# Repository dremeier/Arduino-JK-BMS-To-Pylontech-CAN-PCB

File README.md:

<div align = center>

# [Arduino JK-BMS to Pylontech-CAN PCB](https://github.com/dremeier/Arduino-JK-BMS-To-Pylontech-CAN-PCB) 

PCB and Case for the Arduino JK-BMS To Pylontech-CAN converter for Deye Inverter
<br/>

<br/>
<div align = left>
  
## Arduino Firmware by Armin: https://github.com/ArminJo/JK-BMSToPylontechCAN 

#### If you find this program useful, please give it a star.

&#x1F30E; [Google Translate](https://translate.google.com/translate?sl=en&u=https://github.com/dremeier/Arduino-JK-BMS-To-Pylontech-CAN-PCB)

## Features 
- Buck converter for up to 65 Volt to 5V.
- RS232-stream from the BMS translate from 3,3V to 5V and are galvanic seperated.
- MCU ATmega644P with [MightyCore](https://github.com/MCUdude/MightyCore) Bootloader.
- Connectors are JST PH S4B-PH-K 1x04 P2.00mm Horizontal.
- RJ45 connector Amphenol 54602-x08 Horizontal.
- Designed with KiCad 8.

[Files to print your own case](JK-BMS-CAN_Case/)

## Pictures

### PCB Layout

### Aufbau im Gehäuse

### Fertig installiert mit einem BMS, die Verarbeitung für das 2. BMS ist in Arbeit

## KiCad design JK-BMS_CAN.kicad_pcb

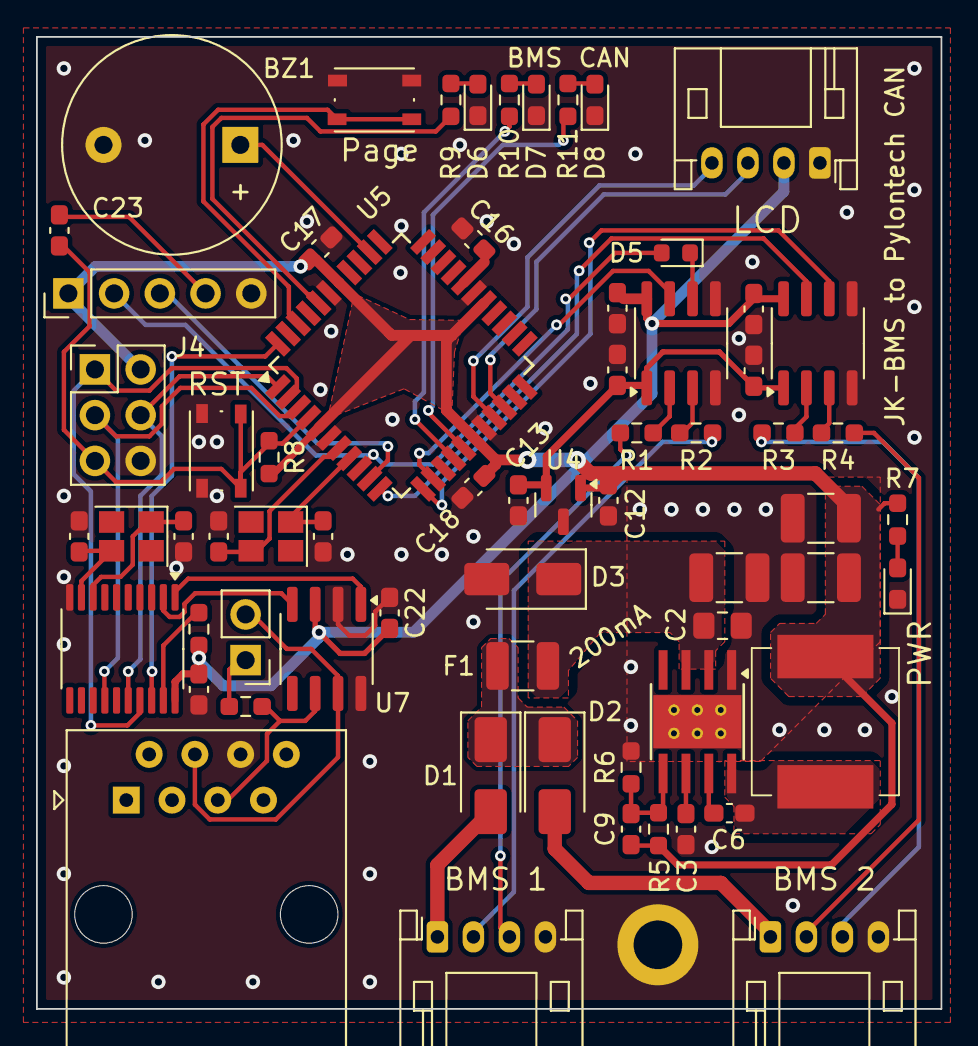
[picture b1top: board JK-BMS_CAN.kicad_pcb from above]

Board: 2 copper layers, 50.2 x 54.0 mm, 66 parts (0 on the bottom side), 53 nets.

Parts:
BZ1: Buzzer; Buzzer_12x9.5RM7.6
C1: 4.7µF/100V; C_1210_3225Metric_Pad1.33x2.70mm_HandSolder
C2: 220nF; C_0805_2012Metric_Pad1.18x1.45mm_HandSolder
C3: 4,7µF/10V; C_0603_1608Metric_Pad1.08x0.95mm_HandSolder
C4, C5, C6, C7, C8, C16, C17, C18, C21, C22, C23: 100nF; C_0603_1608Metric_Pad1.08x0.95mm_HandSolder
C9, C14, C15, C19, C20: 18pF; C_0603_1608Metric_Pad1.08x0.95mm_HandSolder
C10, C11: 47µF/16V; C_1210_3225Metric_Pad1.33x2.70mm_HandSolder
C12, C13: 2,2µF/6,3V; C_0603_1608Metric_Pad1.08x0.95mm_HandSolder
D1, D2: ES2BA; D_SMA
D3: SM6T68A; D_SMA
D4, D7: green 5mA; LED_0603_1608Metric_Pad1.05x0.95mm_HandSolder
D5: CDBU00340; D_0603_1608Metric
D6: red 5mA; LED_0603_1608Metric_Pad1.05x0.95mm_HandSolder
D8: orange 5mA; LED_0603_1608Metric_Pad1.05x0.95mm_HandSolder
F1: 1210L020/72WR; Fuse_1210_3225Metric
H1: MountingHole_Pad; MountingHole_2.7mm_M2.5_ISO7380_Pad
J1: BMS1; JST_PH_S4B-PH-K_1x04_P2.00mm_Horizontal
J2: BMS2; JST_PH_S4B-PH-K_1x04_P2.00mm_Horizontal
J3: Flash; PinHeader_1x05_P2.54mm_Vertical
J4: ICSP; PinHeader_2x03_P2.54mm_Vertical
J5: LCD; JST_PH_S4B-PH-K_1x04_P2.00mm_Horizontal
J6: RJ45; RJ45_Amphenol_54602-x08_Horizontal
JP1: Termi.; PinHeader_1x02_P2.54mm_Vertical
L1: 33µH; IHLP3232DZER330M11
R1, R2, R3, R4: 470; R_0603_1608Metric_Pad0.98x0.95mm_HandSolder
R5: 100K; R_0603_1608Metric_Pad0.98x0.95mm_HandSolder
R6: 24K9; R_0603_1608Metric_Pad0.98x0.95mm_HandSolder
R7, R9, R10, R11: 820; R_0603_1608Metric_Pad0.98x0.95mm_HandSolder
R8: 1K; R_0603_1608Metric_Pad0.98x0.95mm_HandSolder
R12: 10K; R_0603_1608Metric_Pad0.98x0.95mm_HandSolder
R13: 120; R_0603_1608Metric_Pad0.98x0.95mm_HandSolder
SW1: Reset; SW_Push_1P1T_NO_Vertical_Wuerth_434133025816
SW2: Page; SW_Push_1P1T_NO_Vertical_Wuerth_434133025816
U1: LMR36510ADDA; Texas_HTSOP-8-1EP_3.9x4.9mm_P1.27mm_EP2.95x4.9mm_Mask2.4x3.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
U2, U3: ADuM1201AR; SOIC-8_3.9x4.9mm_P1.27mm
U4: AP7384-33SA; SOT-23
U5: ATmega644P-20A; TQFP-44_10x10mm_P0.8mm
U6: MCP2515-xST; TSSOP-20_4.4x6.5mm_P0.65mm
U7: TJA1050T; SOIC-8_3.9x4.9mm_P1.27mm
Y1, Y2: 16MHz; Crystal_SMD_Abracon_ABM8AIG-4Pin_3.2x2.5mm

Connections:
+3.3V: C4.1, C5.1, C13.1, U2.1 (VDD1), U3.1 (VDD1), U4.2 (VO)
+5V: C7.1, C8.1, C9.2, C10.1, C11.1, C12.1, C17.1, C18.1, C21.2, C22.2, J3.1, J4.2, J5.2, L1.2, R5.2, R7.1, R8.2, R12.2, U2.8 (VDD2), U3.8 (VDD2), U4.1 (VI), U5.5 (VCC), U5.17 (VCC), U5.27 (AVCC), U5.38 (VCC), U6.20 (VDD), U7.3 (VCC)
/BMS-1_rx: J1.3, R1.2
/BMS-1_tx: J1.2, R2.2
/BMS-2_rx: J2.3, R3.2
/BMS-2_tx: J2.2, R4.2
/Nano/BMS_Status: R10.1, U5.15 (PD6(D14))
/Nano/Buzz: BZ1.1 (+), U5.35 (A2)
/Nano/CAN-H: J6.4, JP1.2 (B), U7.7 (CANH)
/Nano/CAN-L: J6.5, R13.1, U7.6 (CANL)
/Nano/CAN_Status: R11.1, U5.16 (PD7(D15))
/Nano/CS: U5.44 (~SS), U6.18 (~CS)
/Nano/D2: SW2.1, U5.42 (D2)
/Nano/DTR: C23.2, J3.4
/Nano/LED: R9.1, U5.40 (LED)
/Nano/MISO: J4.1, U5.2 (MISO), U6.17 (SO)
/Nano/MOSI: J4.4, U5.1 (MOSI), U6.16 (SI)
/Nano/SCK: J4.3, U5.3 (SCK), U6.14 (SCK)
/Nano/SCL: J5.4, U5.19 (SCL)
/Nano/SDA: J5.3, U5.20 (SDA)
/Nano/rx_flash: D5.2 (A), J3.2, U5.9 (RXD0)
/Nano/tx_flash: J3.3, U5.10 (TXD0)
/Nano/~RESET: C23.1, J4.5, R8.1, SW1.2, U5.4 (~RESET)
/Vin_BMS1: D1.2 (A), J1.1
/Vin_BMS2: D2.2 (A), J2.1
GND: BZ1.2 (-), C1.2, C2.2, C3.2, C4.2, C5.2, C7.2, C8.2, C10.2, C11.2, C12.2, C13.2, C14.2, C15.2, C16.2, C17.2, C18.2, C19.2, C20.2, C21.1, C22.1, D3.2 (A2), D4.1 (K), D6.1 (K), D7.1 (K), D8.1 (K), H1.1, J1.4, J2.4, J3.5, J4.6, J5.1, J6.6, R6.1, SW1.1, SW2.2, U1.1 (PGND), U1.9 (PAD), U2.4 (GND1), U2.5 (GND2), U3.4 (GND1), U3.5 (GND2), U4.3 (GND), U5.6 (GND), U5.18 (GND), U5.28 (GND), U5.39 (GND), U6.10 (VSS), U7.2 (GND), U7.8 (Rs)
unnamed: D1.1 (K), D2.1 (K), F1.1
unnamed: C1.1, C2.1, D3.1 (A1), F1.2, U1.2 (VIN), U1.3 (EN)
unnamed: D4.2 (A), R7.2
unnamed: D6.2 (A), R9.2
unnamed: D7.2 (A), R10.2
unnamed: D8.2 (A), R11.2
unnamed: JP1.1 (A), R13.2
unnamed: C6.1, U1.7 (BOOT)
unnamed: C9.1, R5.1, R6.2, U1.5 (FB)
unnamed: C6.2, L1.1, U1.8 (SW)
unnamed: C3.1, U1.6 (VCC)
unnamed: R2.1, U2.3 (VIB)
unnamed: R1.1, U2.2 (VOA)
unnamed: R4.1, U3.3 (VIB)
unnamed: R3.1, U3.2 (VOA)
unnamed: C16.1, U5.29 (AREF)
unnamed: C14.1, U5.8 (XTAL1), Y1.1
unnamed: C15.1, U5.7 (XTAL2), Y1.3
unnamed: C20.1, U6.9 (OSC1), Y2.3
unnamed: C19.1, U6.8 (OSC2), Y2.1
unnamed: U6.2 (RXCAN), U7.4 (R)
unnamed: U6.1 (TXCAN), U7.1 (D)
unnamed: R12.1, U6.19 (~RESET)
nano1_rx: D5.1 (K), U2.6 (VOB)
nano1_tx: U2.7 (VIA), U5.13 (PD4(D12))
nano2_rx: U3.6 (VOB), U5.12 (TXD1)
nano2_tx: U3.7 (VIA), U5.11 (RXD1)

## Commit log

2024-05-30 first upload
2024-05-31 changed the crystal to 16MHz
2024-05-31 Rename BMS-CAN_sch.pdf to JK-BMS_to_CAN_sch.pdf
2024-05-31 update the schematic
2024-05-31 Update the BOM
2024-06-11 updated the Case files
2024-06-11 changed the shape to fit the I2C-PCB
2024-06-11 changed to R1.1
    added DTR-line for easy flashing
2024-06-11 added PCB pics for rev1.1
2024-06-12 changed to rev 1.1
    added DTR line for easy flashing
2024-06-12 changed to rev 1.1
